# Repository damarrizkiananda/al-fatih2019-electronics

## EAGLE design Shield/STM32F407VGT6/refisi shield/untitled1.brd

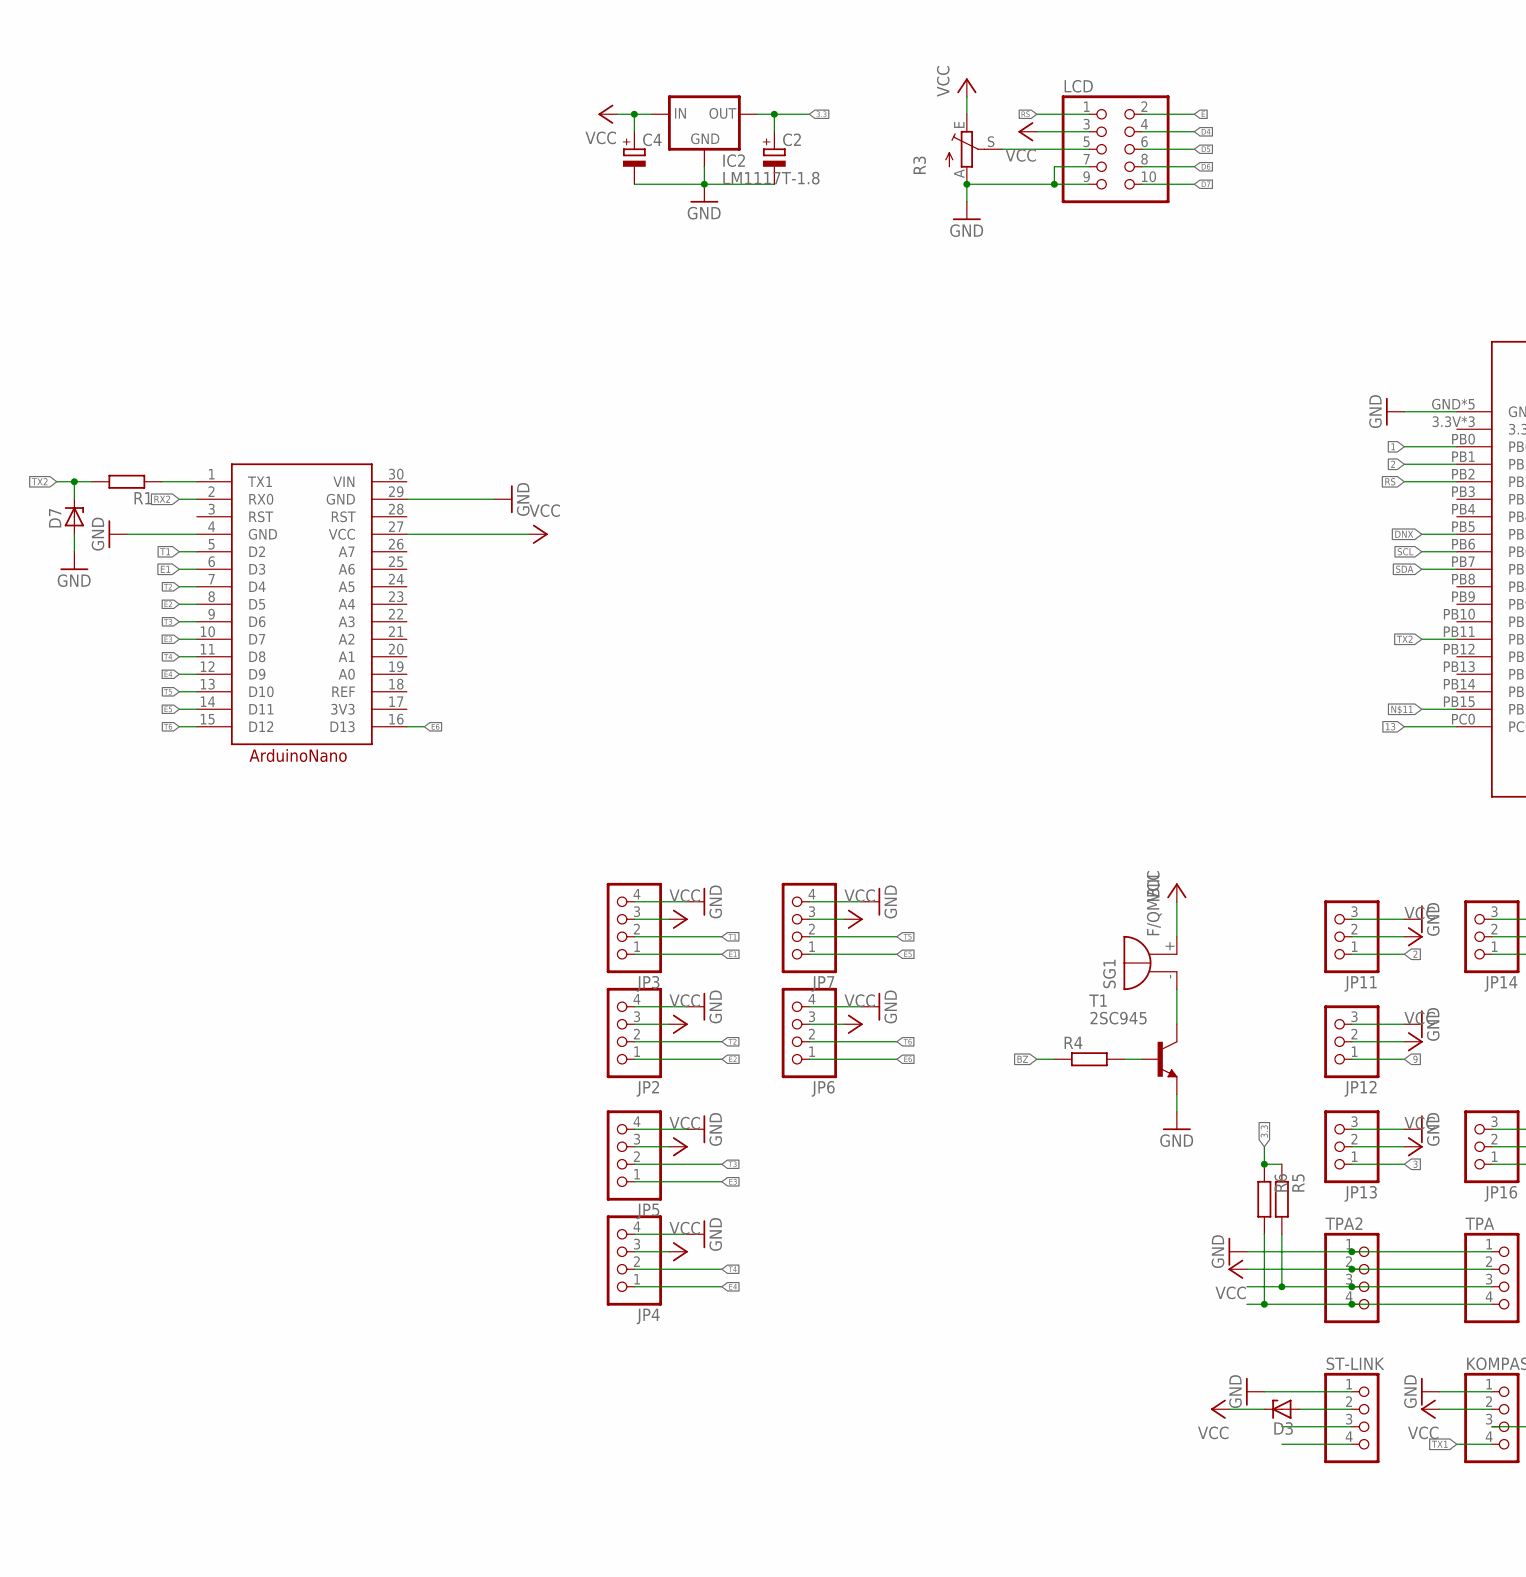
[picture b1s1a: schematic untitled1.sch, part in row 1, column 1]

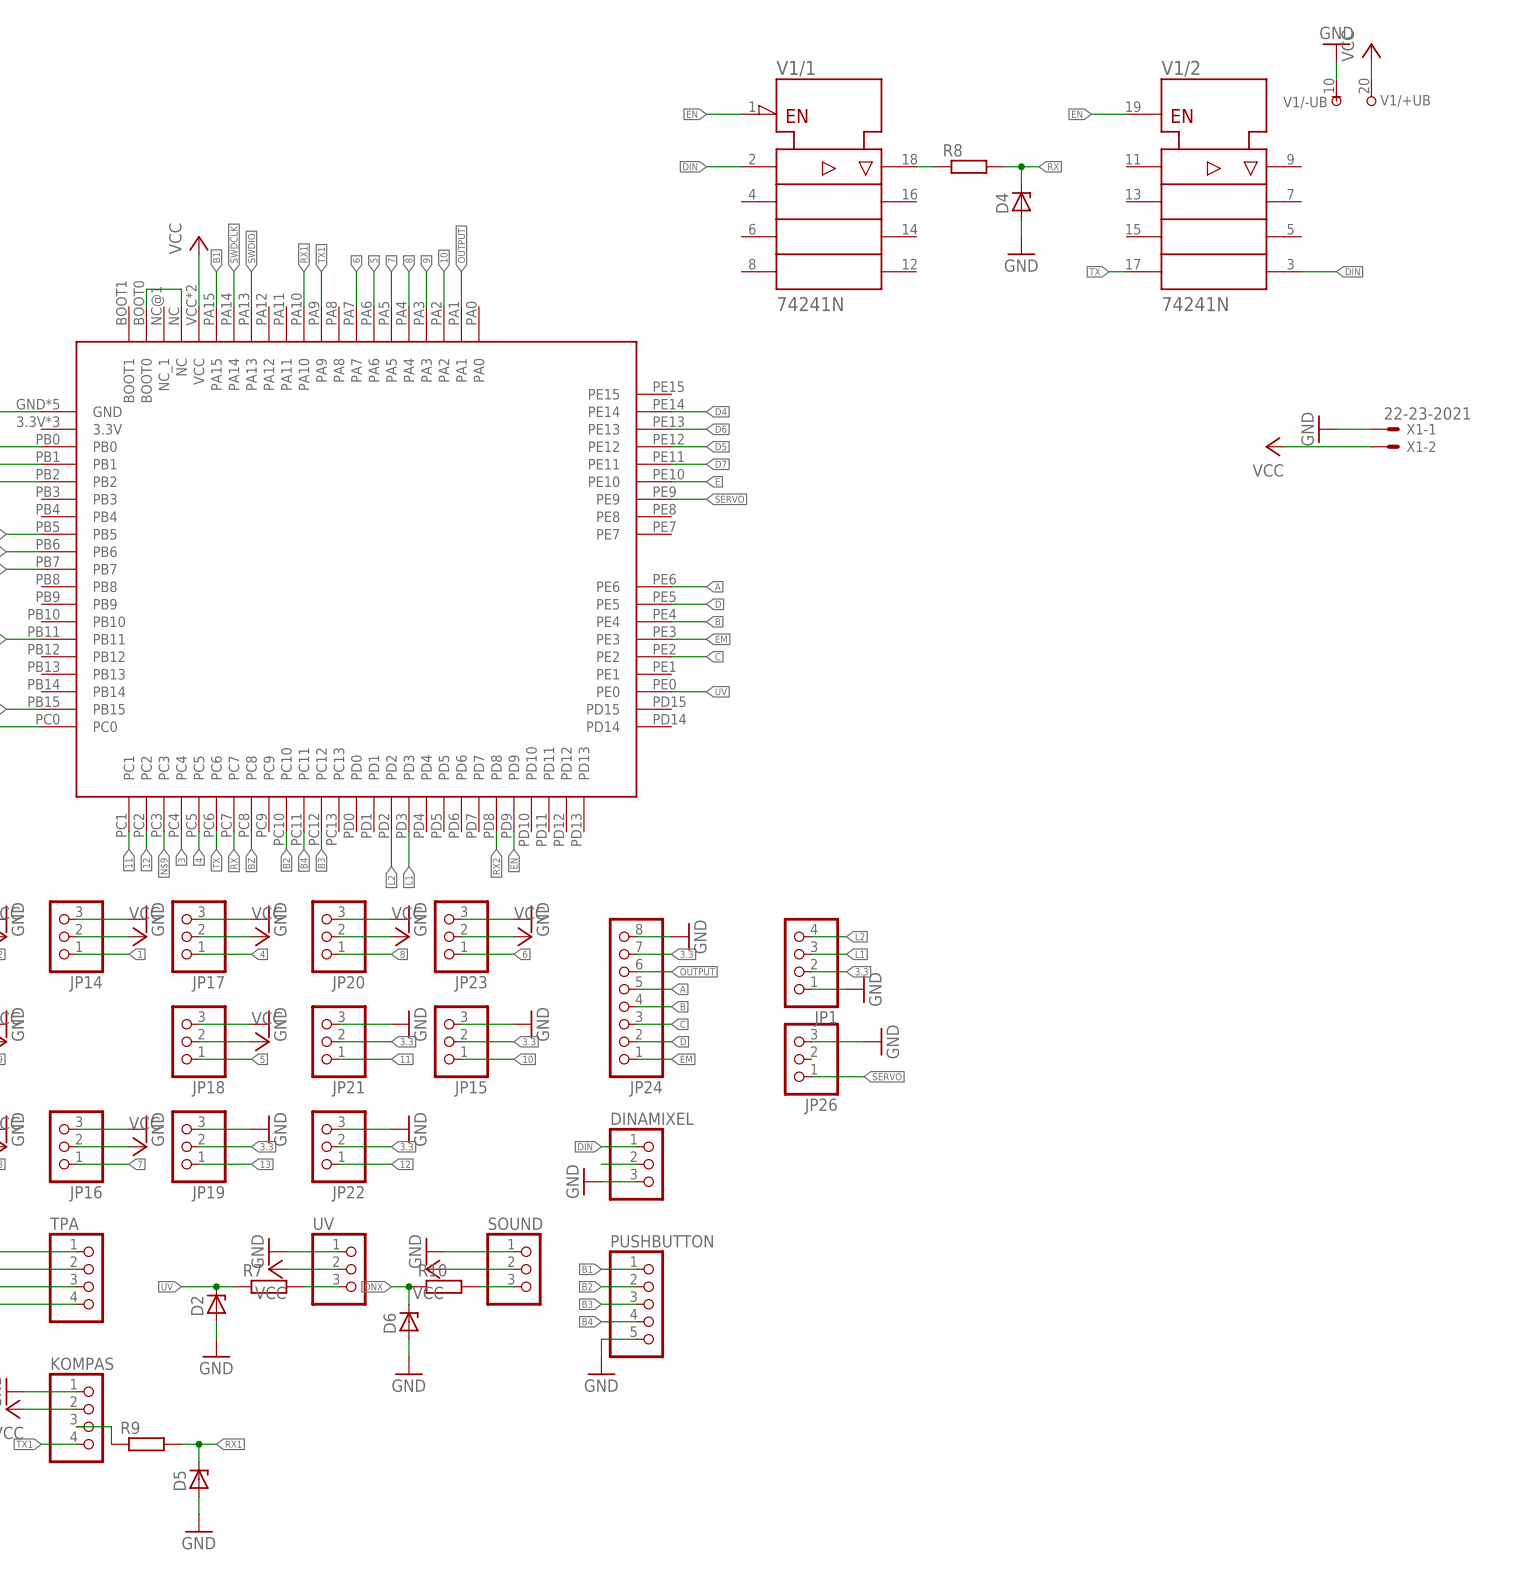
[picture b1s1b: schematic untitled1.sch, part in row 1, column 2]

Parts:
A1: ARDUINONANO
C2, C4: CPOL-EUE2.5-5; E2,5-5
D2, D3, D4, D5, D6, D7: ZENER-DIODEDO34-7; DO34Z7
DINAMIXEL: PINHD-1X3; 1X03
IC2: LM1117T-1.8; TO220
JP1, JP2, JP3, JP4, JP5, JP6, JP7: PINHD-1X4; 1X04
JP11, JP12, JP13, JP14, JP15, JP16, JP17, JP18, JP19, JP20, JP21, JP22, JP23, JP26: PINHD-1X3; 1X03
JP24: PINHD-1X8; 1X08
KOMPAS: PINHD-1X4; 1X04
LCD: PINHD-2X5; 2X05
PUSHBUTTON: PINHD-1X5; 1X05
R1, R4, R5, R6, R7, R8, R9, R10: R-EU_0204/7; 0204/7
R3: TRIM_EU-CA6V; CA6V
SG1: F/QMBIII
SOUND: PINHD-1X3; 1X03
ST-LINK: PINHD-1X4; 1X04
T1: 2SC945; TO92-ECB
TPA, TPA2: PINHD-1X4; 1X04
U$1: STM32F4
UV: PINHD-1X3; 1X03
V1: 74241N; DIL20
X1: 22-23-2021

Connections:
1: JP14.1, U$1.PB0
2: JP11.1, U$1.PB1
3: JP13.1, U$1.PC4
3.3: C2.+, IC2.2 (OUT), JP1.2, JP15.2, JP19.2, JP21.2, JP22.2, JP24.7, R5.1, R6.1
3V3: A1.17 (3V3)
4: JP17.1, U$1.PC5
5: JP18.1, U$1.PA6
6: JP23.1, U$1.PA7
7: JP16.1, U$1.PA5
8: JP20.1, U$1.PA4
9: JP12.1, U$1.PA3
10: JP15.1, U$1.PA2
11: JP21.1, U$1.PC1
12: JP22.1, U$1.PC2
13: JP19.1, U$1.PC0
A: JP24.5, U$1.PE6
B: JP24.4, U$1.PE4
B1: PUSHBUTTON.1, U$1.PA15
B2: PUSHBUTTON.2, U$1.PC10
B3: PUSHBUTTON.3, U$1.PC12
B4: PUSHBUTTON.4, U$1.PC11
BZ: R4.1, U$1.PC8
C: JP24.3, U$1.PE2
D: JP24.2, U$1.PE5
D4: LCD.4, U$1.PE14
D5: LCD.6, U$1.PE12
D6: LCD.8, U$1.PE13
D7: LCD.10, U$1.PE11
DIN: DINAMIXEL.1, V1.2 (A1), V1.3 (Y4)
DNX: D6.C, R10.1, U$1.PB5
E: LCD.2, U$1.PE10
E1: A1.6 (D3), JP3.1
E2: A1.8 (D5), JP2.1
E3: A1.10 (D7), JP5.1
E4: A1.12 (D9), JP4.1
E5: A1.14 (D11), JP7.1
E6: A1.16 (D13), JP6.1
EM: JP24.1, U$1.PE3
EN: U$1.PD9, V1.1 (!G), V1.19 (G)
GND: A1.4 (GND), A1.29 (GND), C2.-, C4.-, D2.A, D4.A, D5.A, D6.A, D7.A, DINAMIXEL.3, IC2.1 (GND), JP1.1, JP2.4, JP3.4, JP4.4, JP5.4, JP6.4, JP7.4, JP11.3, JP12.3, JP13.3, JP14.3, JP15.3, JP16.3, JP17.3, JP18.3, JP19.3, JP20.3, JP21.3, JP22.3, JP23.3, JP24.8, JP26.3, KOMPAS.1, LCD.7, LCD.9, PUSHBUTTON.5, R3.A, SOUND.1, ST-LINK.1, T1.E, TPA.1, TPA2.1, U$1.GND, U$1.GND@1 (GND), U$1.GND@2 (GND), U$1.GND@3 (GND), U$1.GND@5 (GND), UV.1, V1.10 (-UB), X1.1
L1: JP1.3, U$1.PD3
L2: JP1.4, U$1.PD2
unnamed: A1.1 (TX1), R1.1
unnamed: D3.A, ST-LINK.2
unnamed: KOMPAS.3, R9.1
unnamed: R7.2, UV.3
unnamed: LCD.5, R3.S
unnamed: R8.1, V1.18 (Y1)
unnamed: R10.2, SOUND.3
unnamed: U$1.BOOT0, U$1.NC
unnamed: SG1.- (+), T1.C
unnamed: R4.2, T1.B
OUTPUT: JP24.6, U$1.PA1
REF: A1.18 (REF)
RS: LCD.1, U$1.PB2
RX: D4.C, R8.2, U$1.PC7
RX1: D5.C, R9.2, U$1.PA10
RX2: A1.2 (RX0), U$1.PD8
SCL: R6.2, TPA.4, TPA2.4, U$1.PB6
SDA: R5.2, TPA.3, TPA2.3, U$1.PB7
SERVO: JP26.1, U$1.PE9
SWDCLK: ST-LINK.3, U$1.PA14
SWDIO: ST-LINK.4, U$1.PA13
T1: A1.5 (D2), JP3.2
T2: A1.7 (D4), JP2.2
T3: A1.9 (D6), JP5.2
T4: A1.11 (D8), JP4.2
T5: A1.13 (D10), JP7.2
T6: A1.15 (D12), JP6.2
TX: U$1.PC6, V1.17 (A4)
TX1: KOMPAS.4, U$1.PA9
TX2: D7.C, R1.2, U$1.PB11
UV: D2.C, R7.1, U$1.PE0
VCC: A1.27 (VCC), C4.+, D3.C, IC2.3 (IN), JP2.3, JP3.3, JP4.3, JP5.3, JP6.3, JP7.3, JP11.2, JP12.2, JP13.2, JP14.2, JP16.2, JP17.2, JP18.2, JP20.2, JP23.2, KOMPAS.2, LCD.3, R3.E, SG1.+ (-), SOUND.2, TPA.2, TPA2.2, U$1.VCC, U$1.VCC@1 (VCC), UV.2, V1.20 (+UB), X1.2
VIN: A1.30 (VIN)

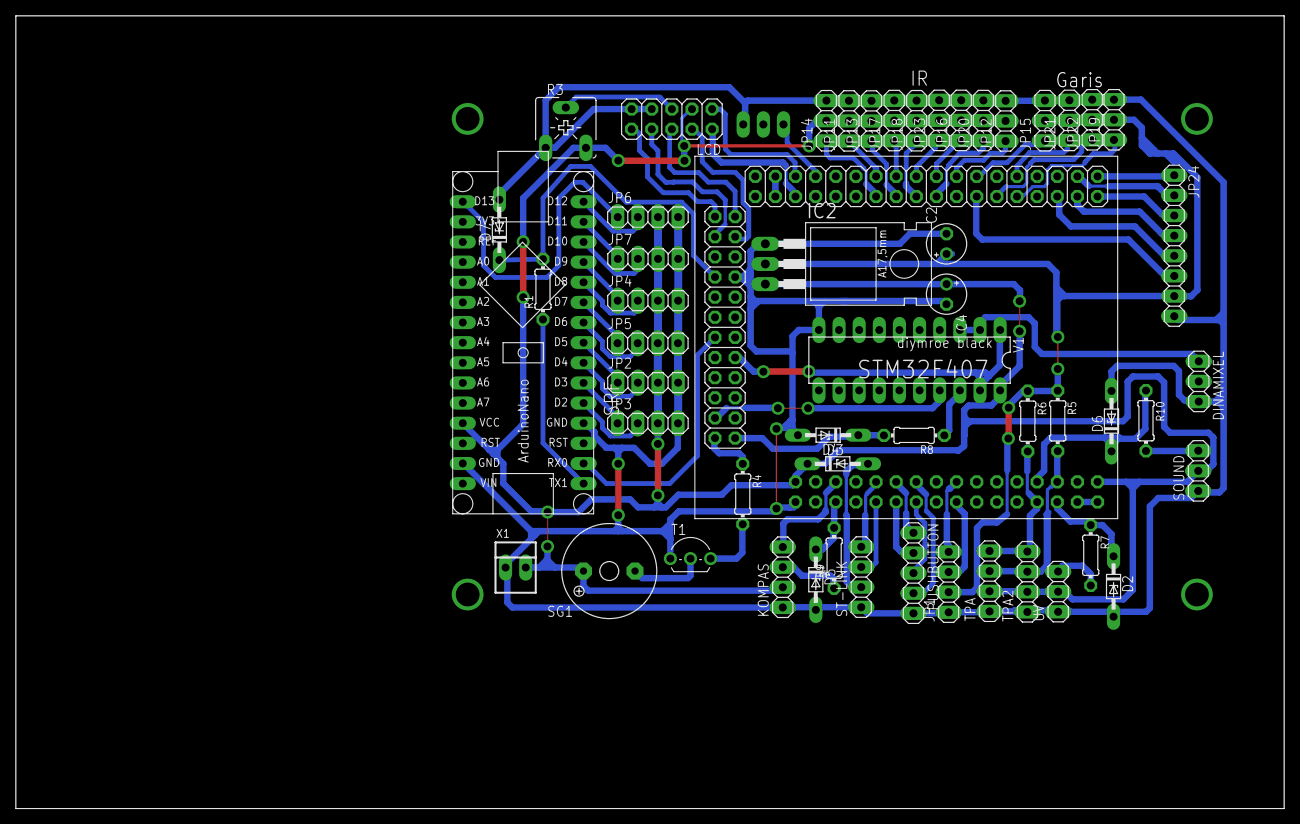
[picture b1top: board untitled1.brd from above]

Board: 2 copper layers, 160.0 x 100.0 mm, 55 parts (1 on the bottom side), 72 nets.

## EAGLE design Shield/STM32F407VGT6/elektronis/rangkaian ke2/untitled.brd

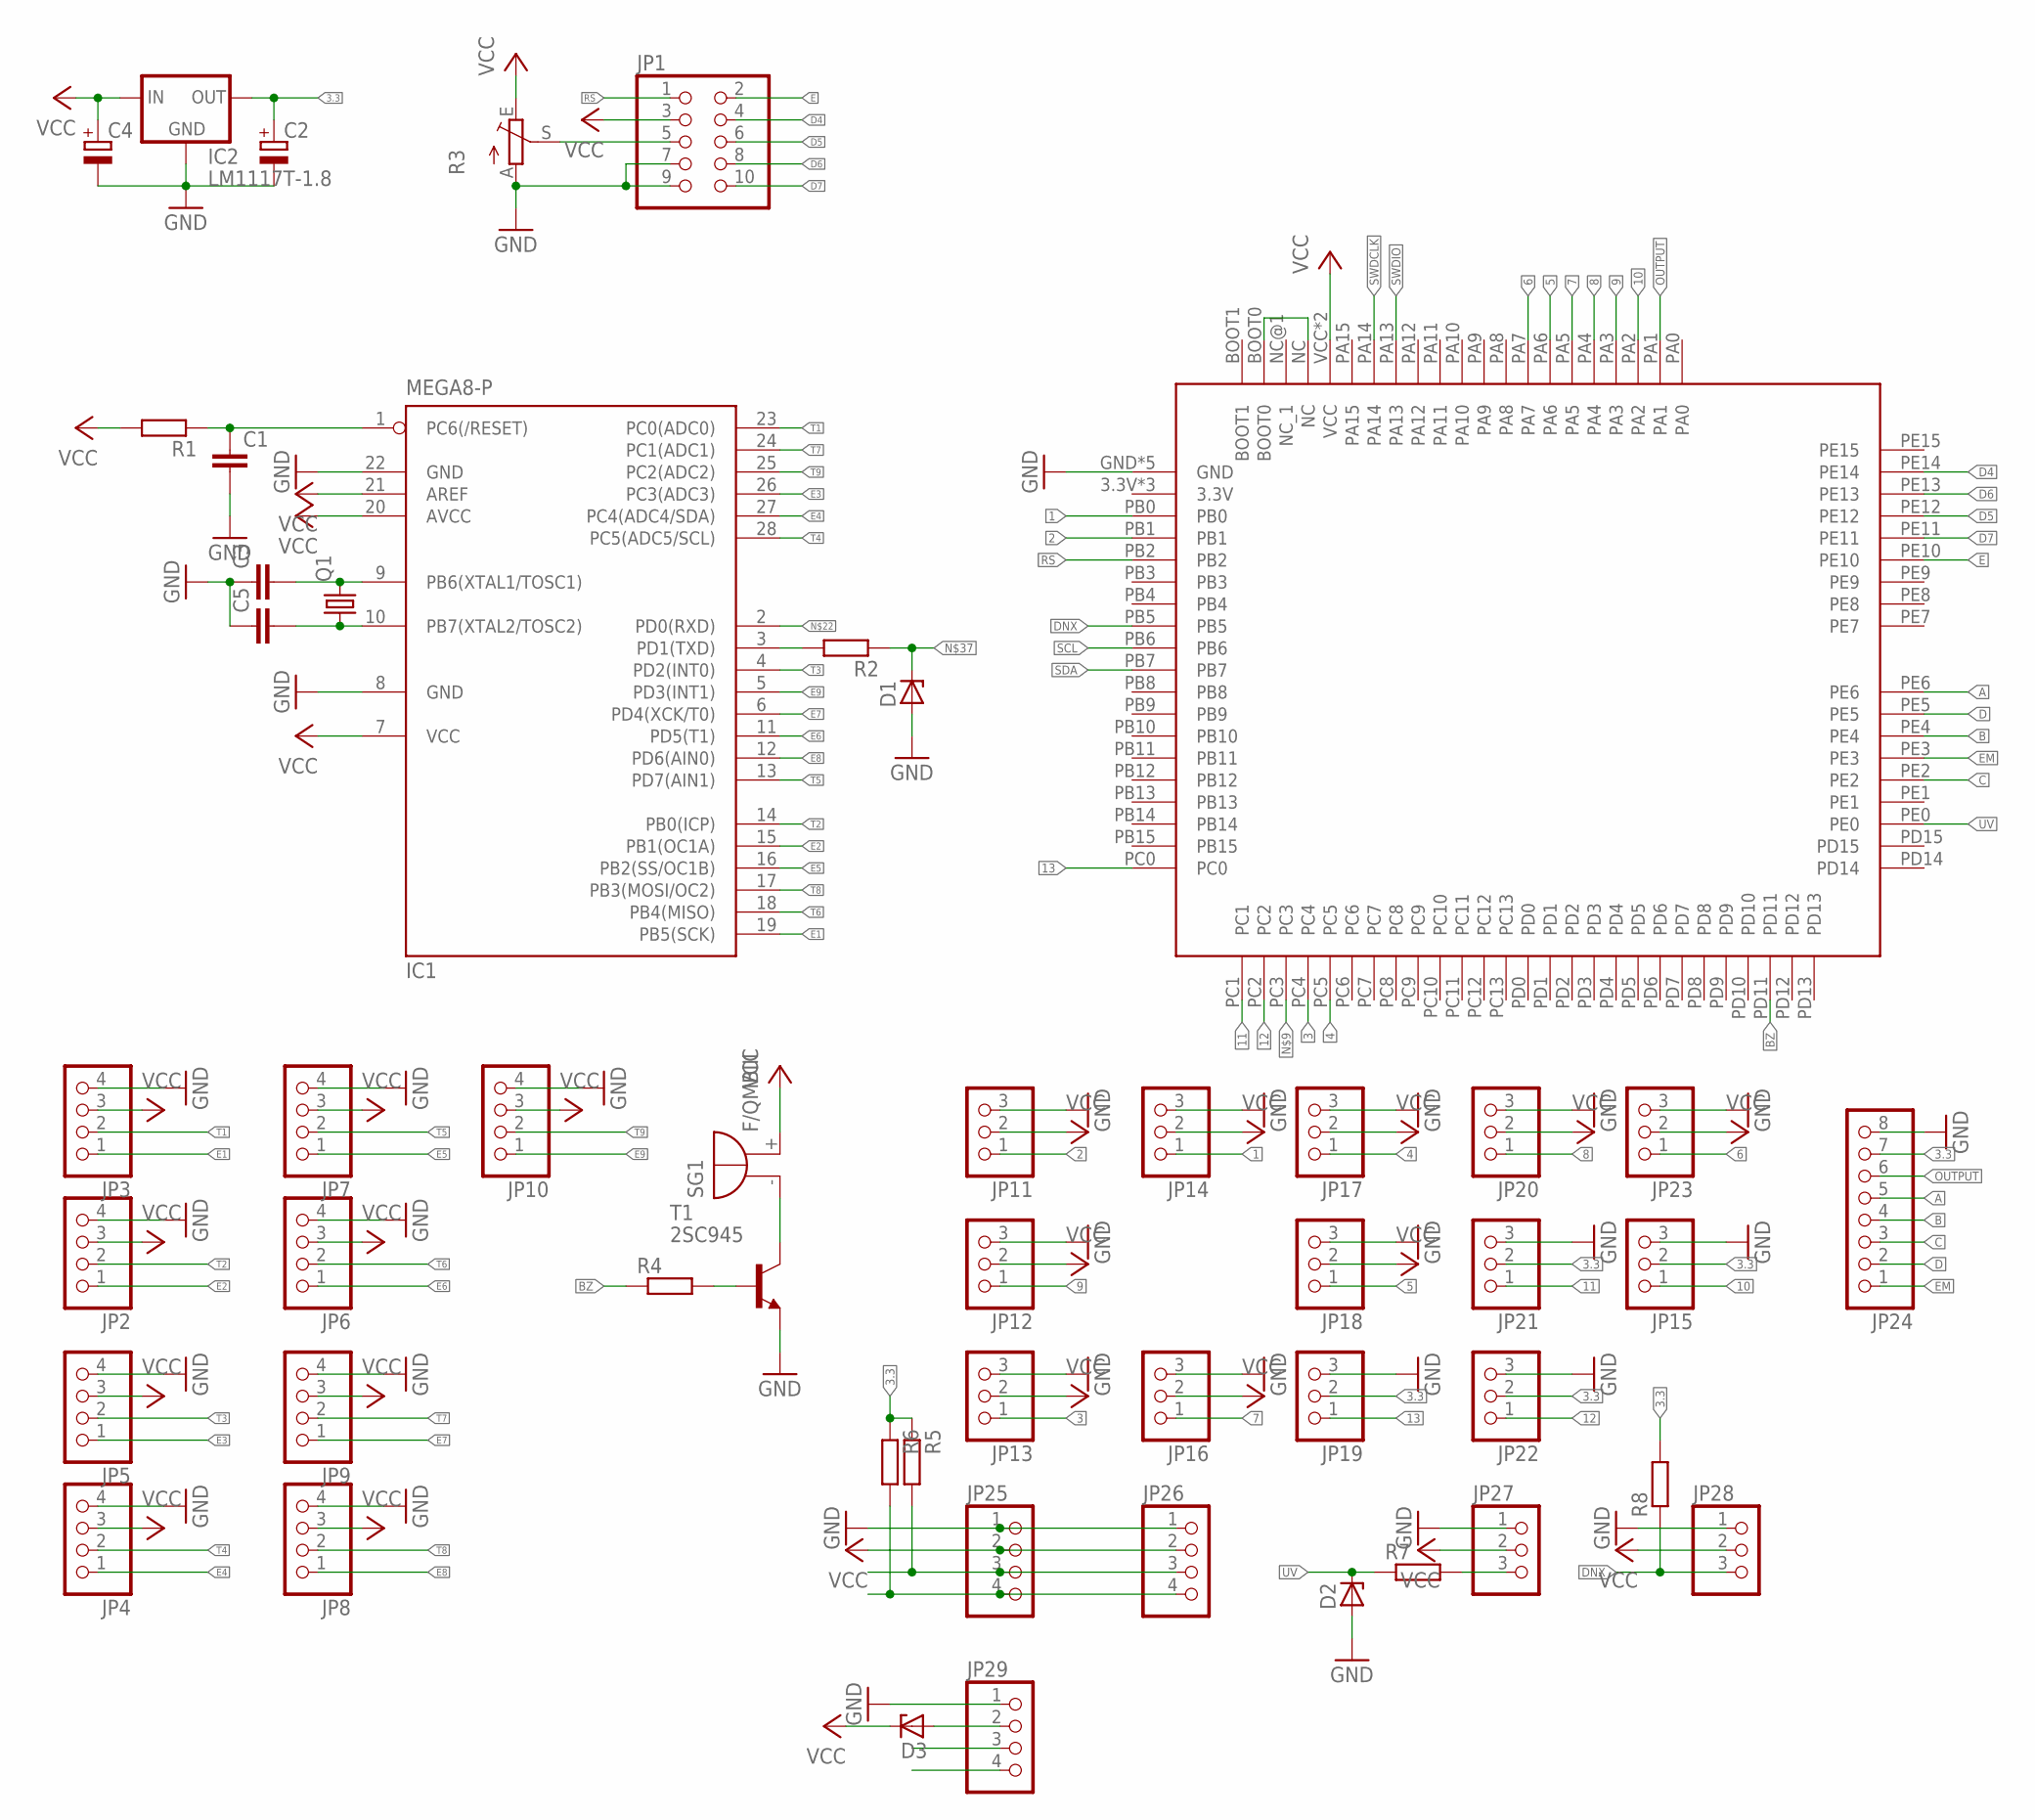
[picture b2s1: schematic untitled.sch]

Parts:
C1, C3, C5: C-EU025-025X050; C025-025X050
C2, C4: CPOL-EUE2.5-5; E2,5-5
D1, D2, D3: ZENER-DIODEDO34-7; DO34Z7
IC1: MEGA8-P; DIL28-3
IC2: LM1117T-1.8; TO220
JP1: PINHD-2X5; 2X05
JP2, JP3, JP4, JP5, JP6, JP7, JP8, JP9, JP10, JP25, JP26, JP29: PINHD-1X4; 1X04
JP11, JP12, JP13, JP14, JP15, JP16, JP17, JP18, JP19, JP20, JP21, JP22, JP23, JP27, JP28: PINHD-1X3; 1X03
JP24: PINHD-1X8; 1X08
Q1: CRYSTALHC49U70; HC49U70
R1, R2, R4, R5, R6, R7, R8: R-EU_0204/7; 0204/7
R3: TRIM_EU-CA6V; CA6V
SG1: F/QMBIII
T1: 2SC945; TO92-ECB
U$1: STM32F4

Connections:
1: JP14.1, U$1.PB0
2: JP11.1, U$1.PB1
3: JP13.1, U$1.PC4
3.3: C2.+, IC2.2 (OUT), JP15.2, JP19.2, JP21.2, JP22.2, JP24.7, R5.1, R6.1, R8.2
4: JP17.1, U$1.PC5
5: JP18.1, U$1.PA6
6: JP23.1, U$1.PA7
7: JP16.1, U$1.PA5
8: JP20.1, U$1.PA4
9: JP12.1, U$1.PA3
10: JP15.1, U$1.PA2
11: JP21.1, U$1.PC1
12: JP22.1, U$1.PC2
13: JP19.1, U$1.PC0
A: JP24.5, U$1.PE6
B: JP24.4, U$1.PE4
BZ: R4.1, U$1.PD11
C: JP24.3, U$1.PE2
D: JP24.2, U$1.PE5
D4: JP1.4, U$1.PE14
D5: JP1.6, U$1.PE12
D6: JP1.8, U$1.PE13
D7: JP1.10, U$1.PE11
DNX: JP28.3, R8.1, U$1.PB5
E: JP1.2, U$1.PE10
E1: IC1.19 (PB5(SCK)), JP3.1
E2: IC1.15 (PB1(OC1A)), JP2.1
E3: IC1.26 (PC3(ADC3)), JP5.1
E4: IC1.27 (PC4(ADC4/SDA)), JP4.1
E5: IC1.16 (PB2(SS/OC1B)), JP7.1
E6: IC1.11 (PD5(T1)), JP6.1
E7: IC1.6 (PD4(XCK/T0)), JP9.1
E8: IC1.12 (PD6(AIN0)), JP8.1
E9: IC1.5 (PD3(INT1)), JP10.1
EM: JP24.1, U$1.PE3
GND: C1.2, C2.-, C3.1, C4.-, C5.1, D1.A, D2.A, IC1.8 (GND), IC1.22 (GND), IC2.1 (GND), JP1.7, JP1.9, JP2.4, JP3.4, JP4.4, JP5.4, JP6.4, JP7.4, JP8.4, JP9.4, JP10.4, JP11.3, JP12.3, JP13.3, JP14.3, JP15.3, JP16.3, JP17.3, JP18.3, JP19.3, JP20.3, JP21.3, JP22.3, JP23.3, JP24.8, JP25.1, JP26.1, JP27.1, JP28.1, JP29.1, R3.A, T1.E, U$1.GND, U$1.GND@1 (GND), U$1.GND@2 (GND), U$1.GND@3 (GND), U$1.GND@5 (GND)
unnamed: C1.1, IC1.1 (PC6(/RESET)), R1.1
unnamed: D3.A, JP29.2
unnamed: C5.2, IC1.10 (PB7(XTAL2/TOSC2)), Q1.1
unnamed: C3.2, IC1.9 (PB6(XTAL1/TOSC1)), Q1.2
unnamed: JP27.3, R7.2
unnamed: JP1.5, R3.S
unnamed: U$1.BOOT0, U$1.NC
unnamed: SG1.- (+), T1.C
unnamed: R4.2, T1.B
unnamed: IC1.3 (PD1(TXD)), R2.2
unnamed: D1.C, R2.1
OUTPUT: JP24.6, U$1.PA1
RS: JP1.1, U$1.PB2
SCL: JP25.4, JP26.4, R6.2, U$1.PB6
SDA: JP25.3, JP26.3, R5.2, U$1.PB7
SWDCLK: JP29.3, U$1.PA14
SWDIO: JP29.4, U$1.PA13
T1: IC1.23 (PC0(ADC0)), JP3.2
T2: IC1.14 (PB0(ICP)), JP2.2
T3: IC1.4 (PD2(INT0)), JP5.2
T4: IC1.28 (PC5(ADC5/SCL)), JP4.2
T5: IC1.13 (PD7(AIN1)), JP7.2
T6: IC1.18 (PB4(MISO)), JP6.2
T7: IC1.24 (PC1(ADC1)), JP9.2
T8: IC1.17 (PB3(MOSI/OC2)), JP8.2
T9: IC1.25 (PC2(ADC2)), JP10.2
UV: D2.C, R7.1, U$1.PE0
VCC: C4.+, D3.C, IC1.7 (VCC), IC1.20 (AVCC), IC1.21 (AREF), IC2.3 (IN), JP1.3, JP2.3, JP3.3, JP4.3, JP5.3, JP6.3, JP7.3, JP8.3, JP9.3, JP10.3, JP11.2, JP12.2, JP13.2, JP14.2, JP16.2, JP17.2, JP18.2, JP20.2, JP23.2, JP25.2, JP26.2, JP27.2, JP28.2, R1.2, R3.E, SG1.+ (-), U$1.VCC, U$1.VCC@1 (VCC)

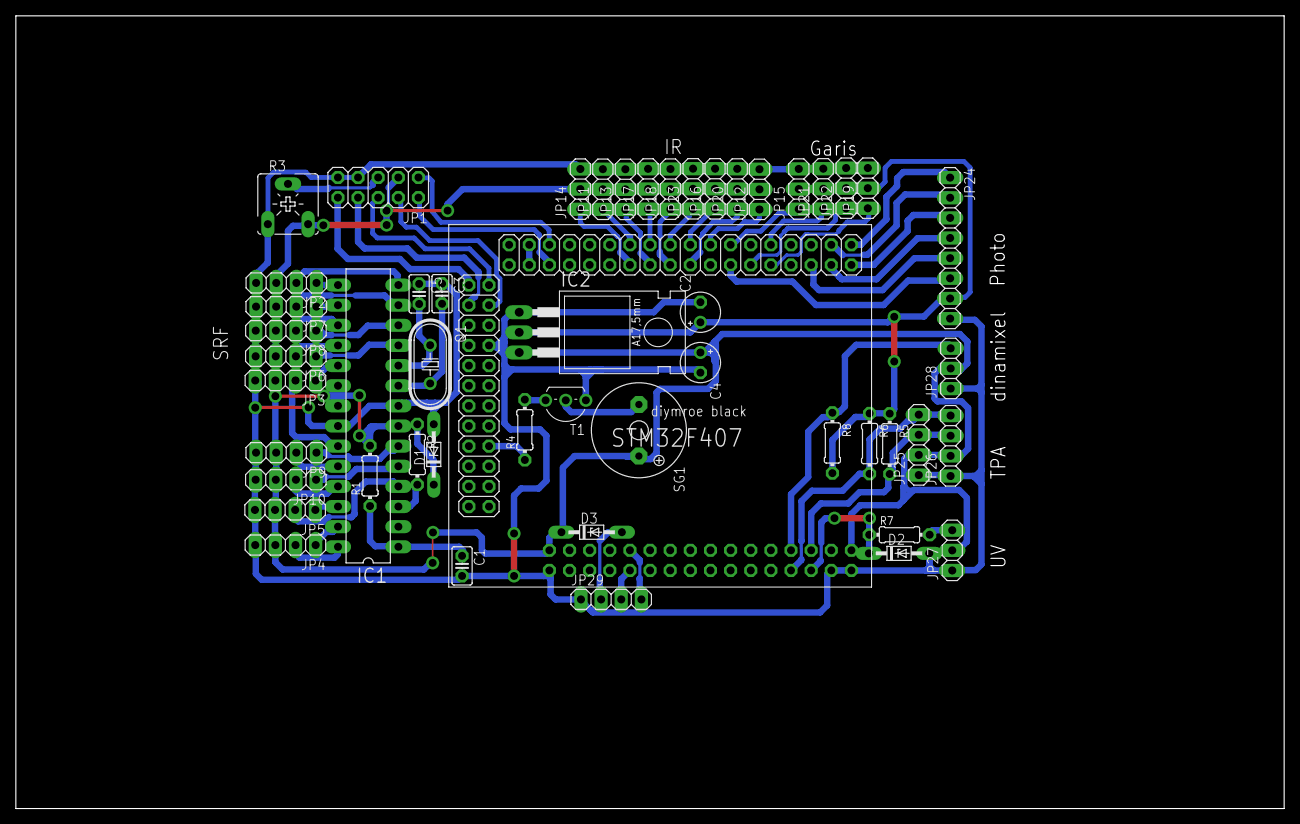
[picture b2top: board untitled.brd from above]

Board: 2 copper layers, 160.0 x 100.0 mm, 51 parts (0 on the bottom side), 64 nets.

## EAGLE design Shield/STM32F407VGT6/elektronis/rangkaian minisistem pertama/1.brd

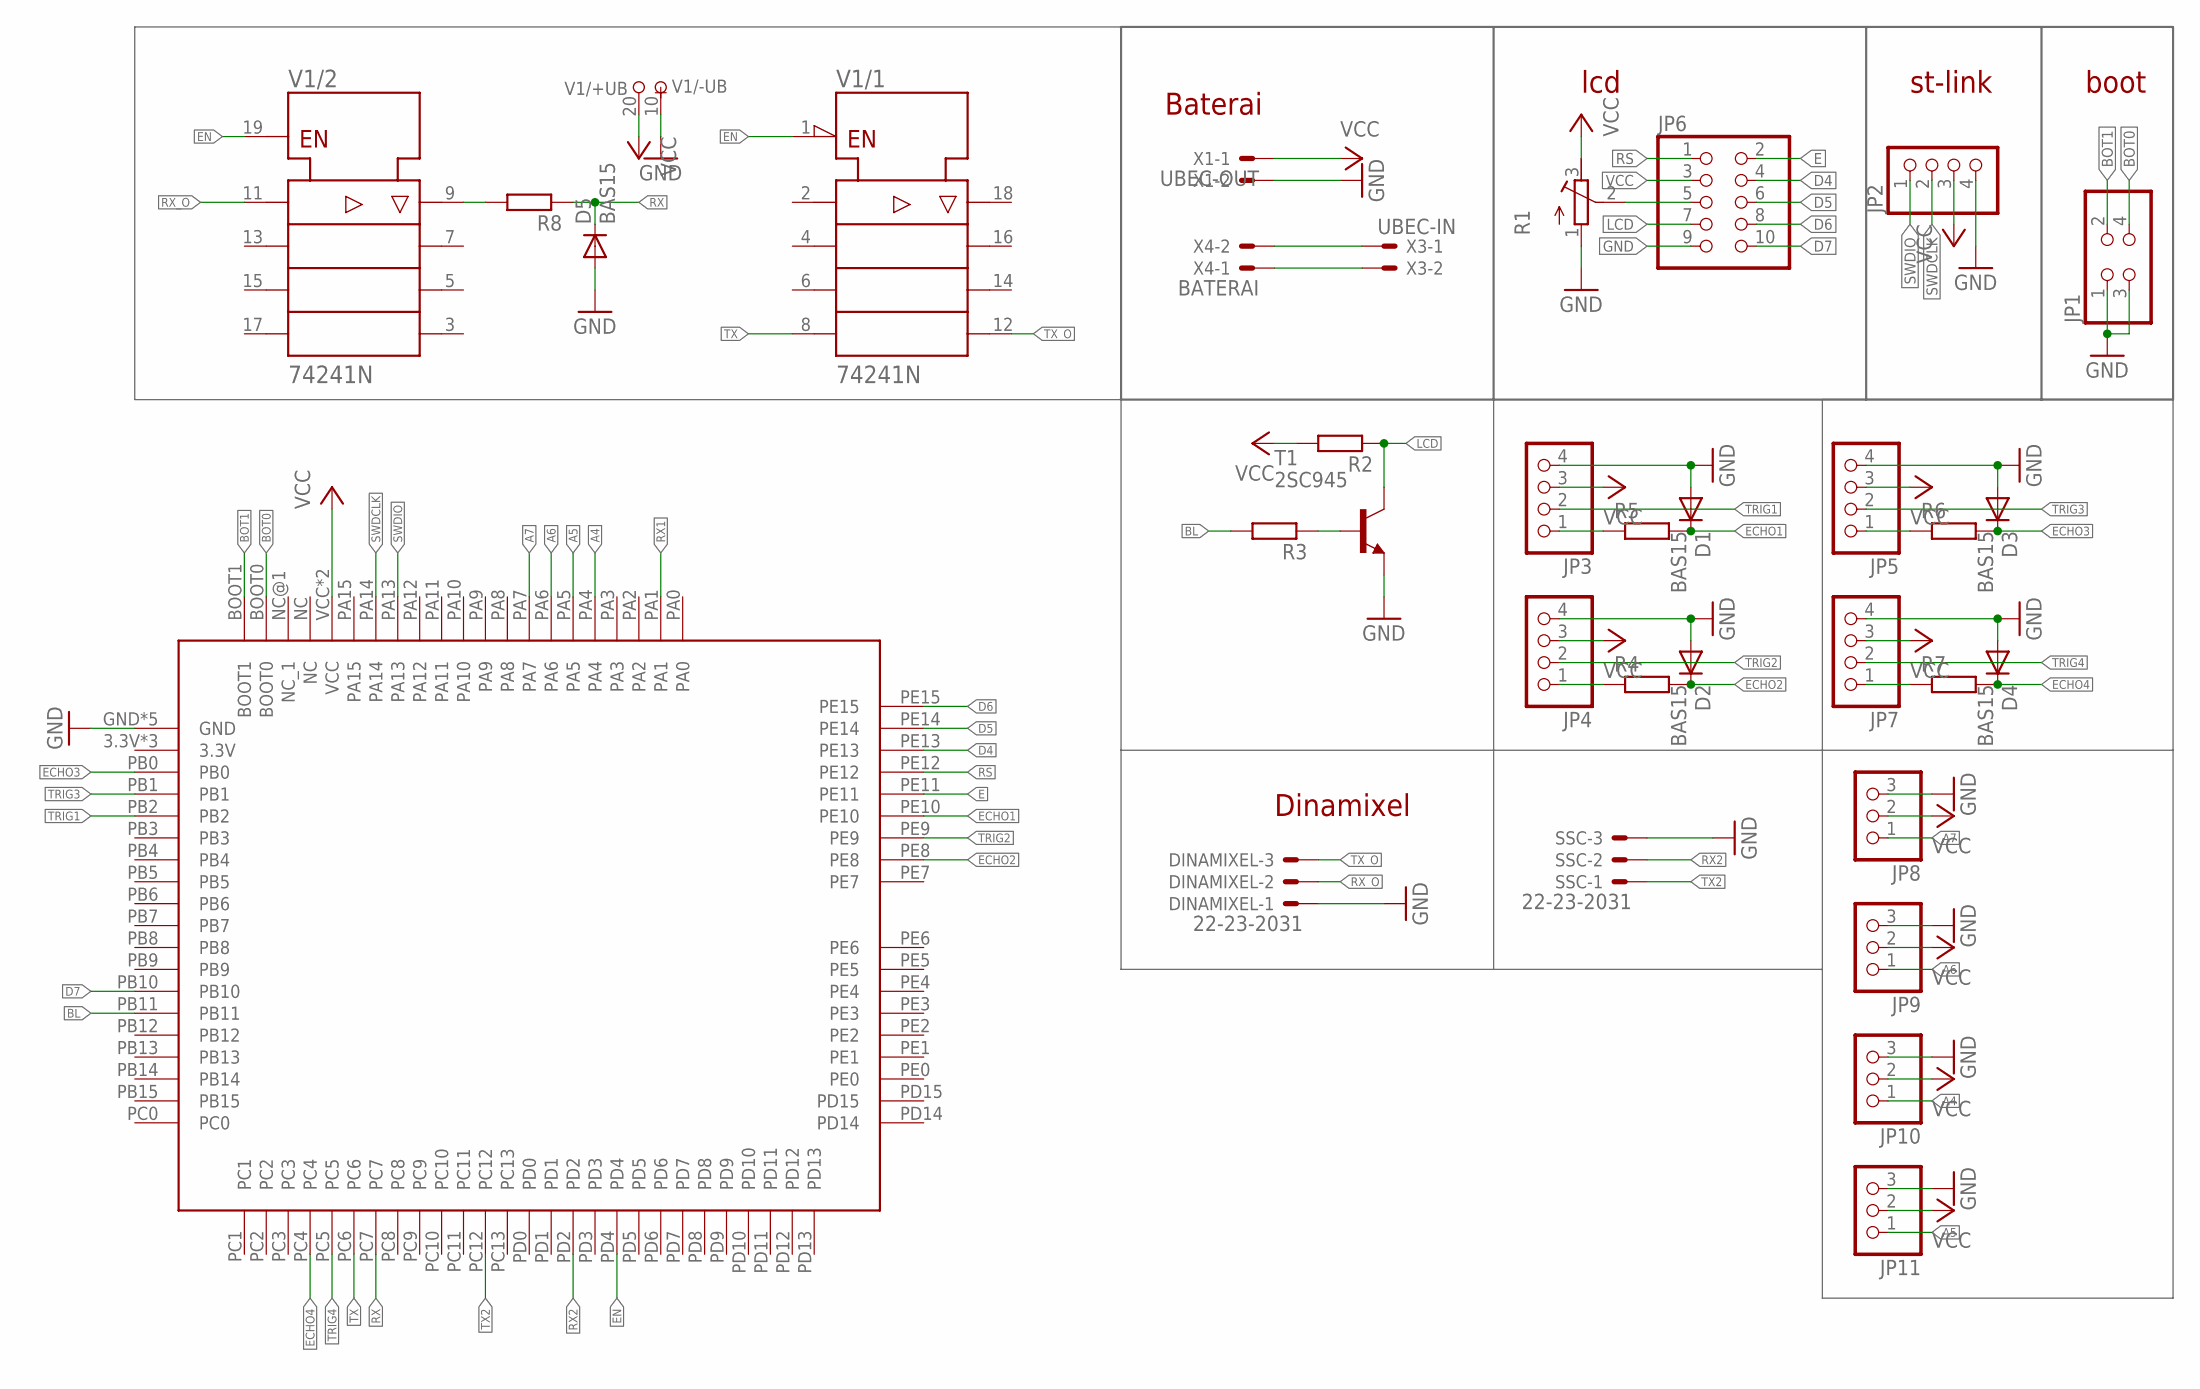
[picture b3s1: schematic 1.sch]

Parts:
D1, D2, D3, D4, D5: BAS15; DO34-7
DINAMIXEL: 22-23-2031
JP1: PINHD-2X2; 2X02
JP2, JP3, JP4, JP5, JP7: PINHD-1X4; 1X04
JP6: PINHD-2X5; 2X05
JP8, JP9, JP10, JP11: PINHD-1X3; 1X03
R1: R-TRIMM3339P; RTRIM3339P
R2, R3, R4, R5, R6, R7, R8: R-EU_0207/7; 0207/7
SSC: 22-23-2031
T1: 2SC945; TO92-ECB
U$2: STM32F4
V1: 74241N; DIL20
X1: UBEC-OUT; 22-23-2021
X3: UBEC-IN; 22-23-2021
X4: BATERAI; 22-23-2021

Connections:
A4: JP10.1, U$2.PA4
A5: JP11.1, U$2.PA5
A6: JP9.1, U$2.PA6
A7: JP8.1, U$2.PA7
BL: R3.2, U$2.PB11
BOT0: JP1.4, U$2.BOOT0
BOT1: JP1.2, U$2.BOOT1
D4: JP6.4, U$2.PE13
D5: JP6.6, U$2.PE14
D6: JP6.8, U$2.PE15
D7: JP6.10, U$2.PB10
E: JP6.2, U$2.PE11
ECHO1: D1.C, R5.2, U$2.PE10
ECHO2: D2.C, R4.2, U$2.PE8
ECHO3: D3.C, R6.2, U$2.PB0
ECHO4: D4.C, R7.2, U$2.PC4
EN: U$2.PD4, V1.1 (!G), V1.19 (G)
GND: D1.A, D2.A, D3.A, D4.A, D5.A, DINAMIXEL.1, JP1.1, JP1.3, JP2.4, JP3.4, JP4.4, JP5.4, JP6.9, JP7.4, JP8.3, JP9.3, JP10.3, JP11.3, R1.1 (A), SSC.3, T1.E, U$2.GND, U$2.GND@1 (GND), U$2.GND@2 (GND), U$2.GND@3 (GND), U$2.GND@5 (GND), V1.10 (-UB), X1.2
LCD: JP6.7, R2.1, T1.C
unnamed: JP4.1, R4.1
unnamed: R3.1, T1.B
unnamed: JP3.1, R5.1
unnamed: X3.1, X4.2
unnamed: X3.2, X4.1
unnamed: JP6.5, R1.2 (S)
unnamed: JP5.1, R6.1
unnamed: JP7.1, R7.1
unnamed: R8.2, V1.9 (Y1)
RS: JP6.1, U$2.PE12
RX: D5.C, R8.1, U$2.PC7
RX1: U$2.PA1
RX2: SSC.2, U$2.PD2
RX_O: DINAMIXEL.2, V1.11 (A1)
SWDCLK: JP2.2, U$2.PA14
SWDIO: JP2.1, U$2.PA13
TRIG1: JP3.2, U$2.PB2
TRIG2: JP4.2, U$2.PE9
TRIG3: JP5.2, U$2.PB1
TRIG4: JP7.2, U$2.PC5
TX: U$2.PC6, V1.8 (A4)
TX2: SSC.1, U$2.PC12
TX_O: DINAMIXEL.3, V1.12 (Y4)
VCC: JP2.3, JP3.3, JP4.3, JP5.3, JP6.3, JP7.3, JP8.2, JP9.2, JP10.2, JP11.2, R1.3 (E), R2.2, U$2.VCC, U$2.VCC@1 (VCC), V1.20 (+UB), X1.1

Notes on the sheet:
st-link
boot
lcd
Baterai
Dinamixel

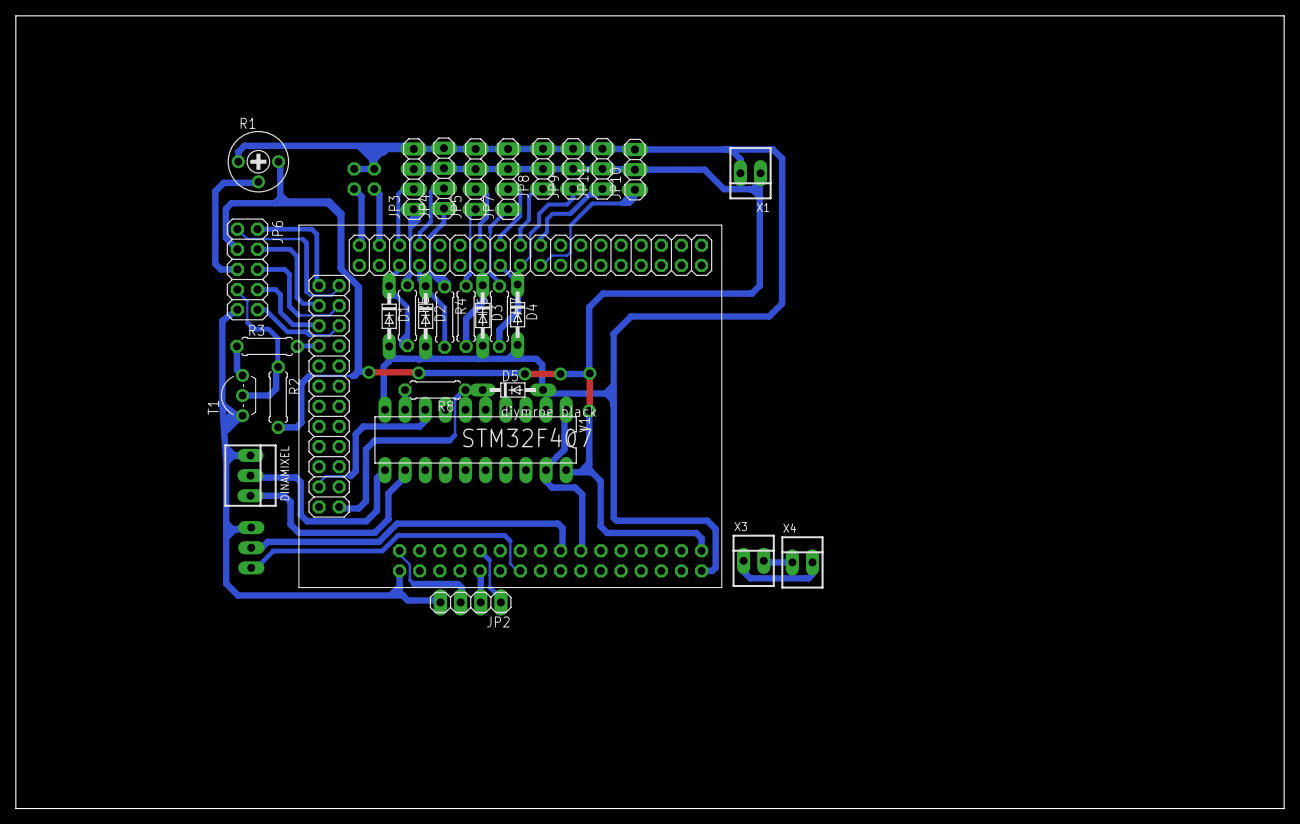
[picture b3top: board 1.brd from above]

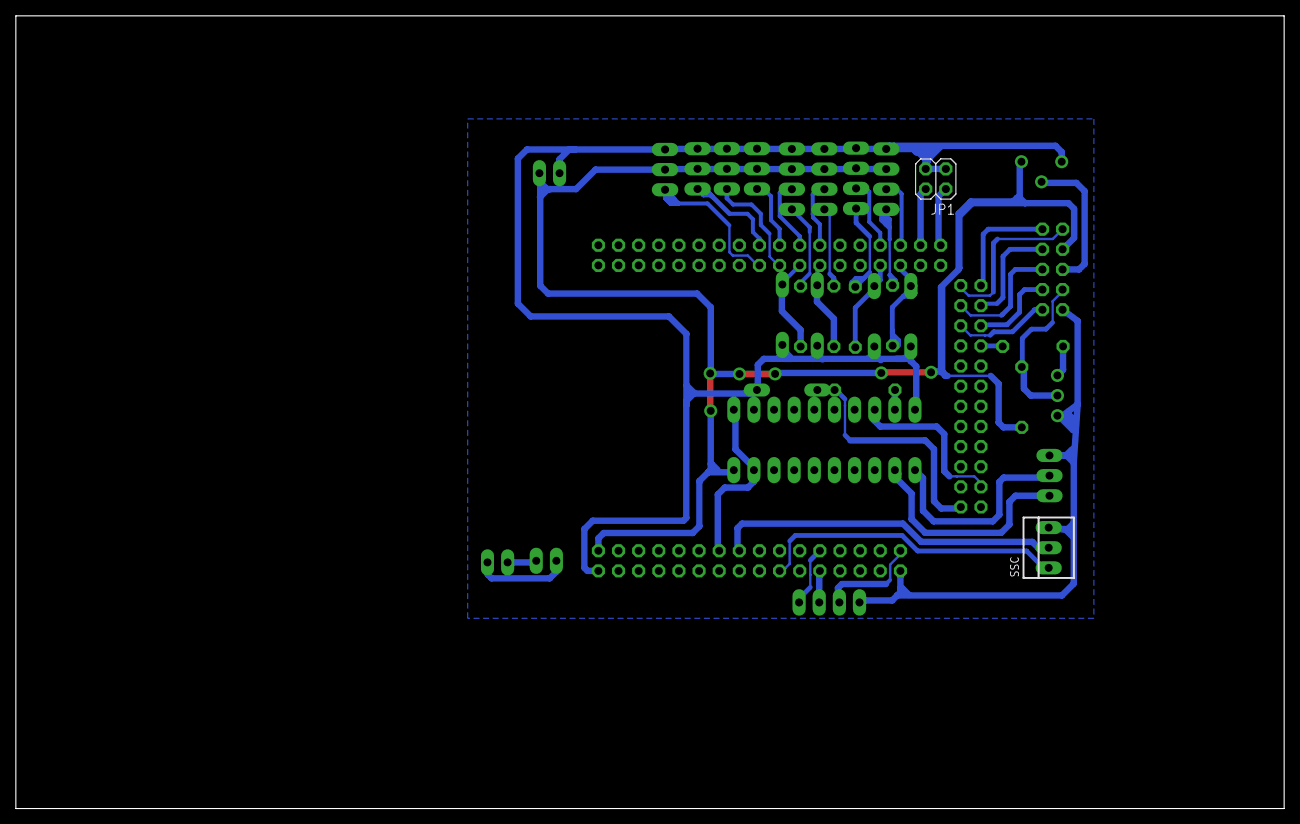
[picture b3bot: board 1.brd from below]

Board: 2 copper layers, 160.0 x 100.0 mm, 32 parts (2 on the bottom side), 42 nets.
